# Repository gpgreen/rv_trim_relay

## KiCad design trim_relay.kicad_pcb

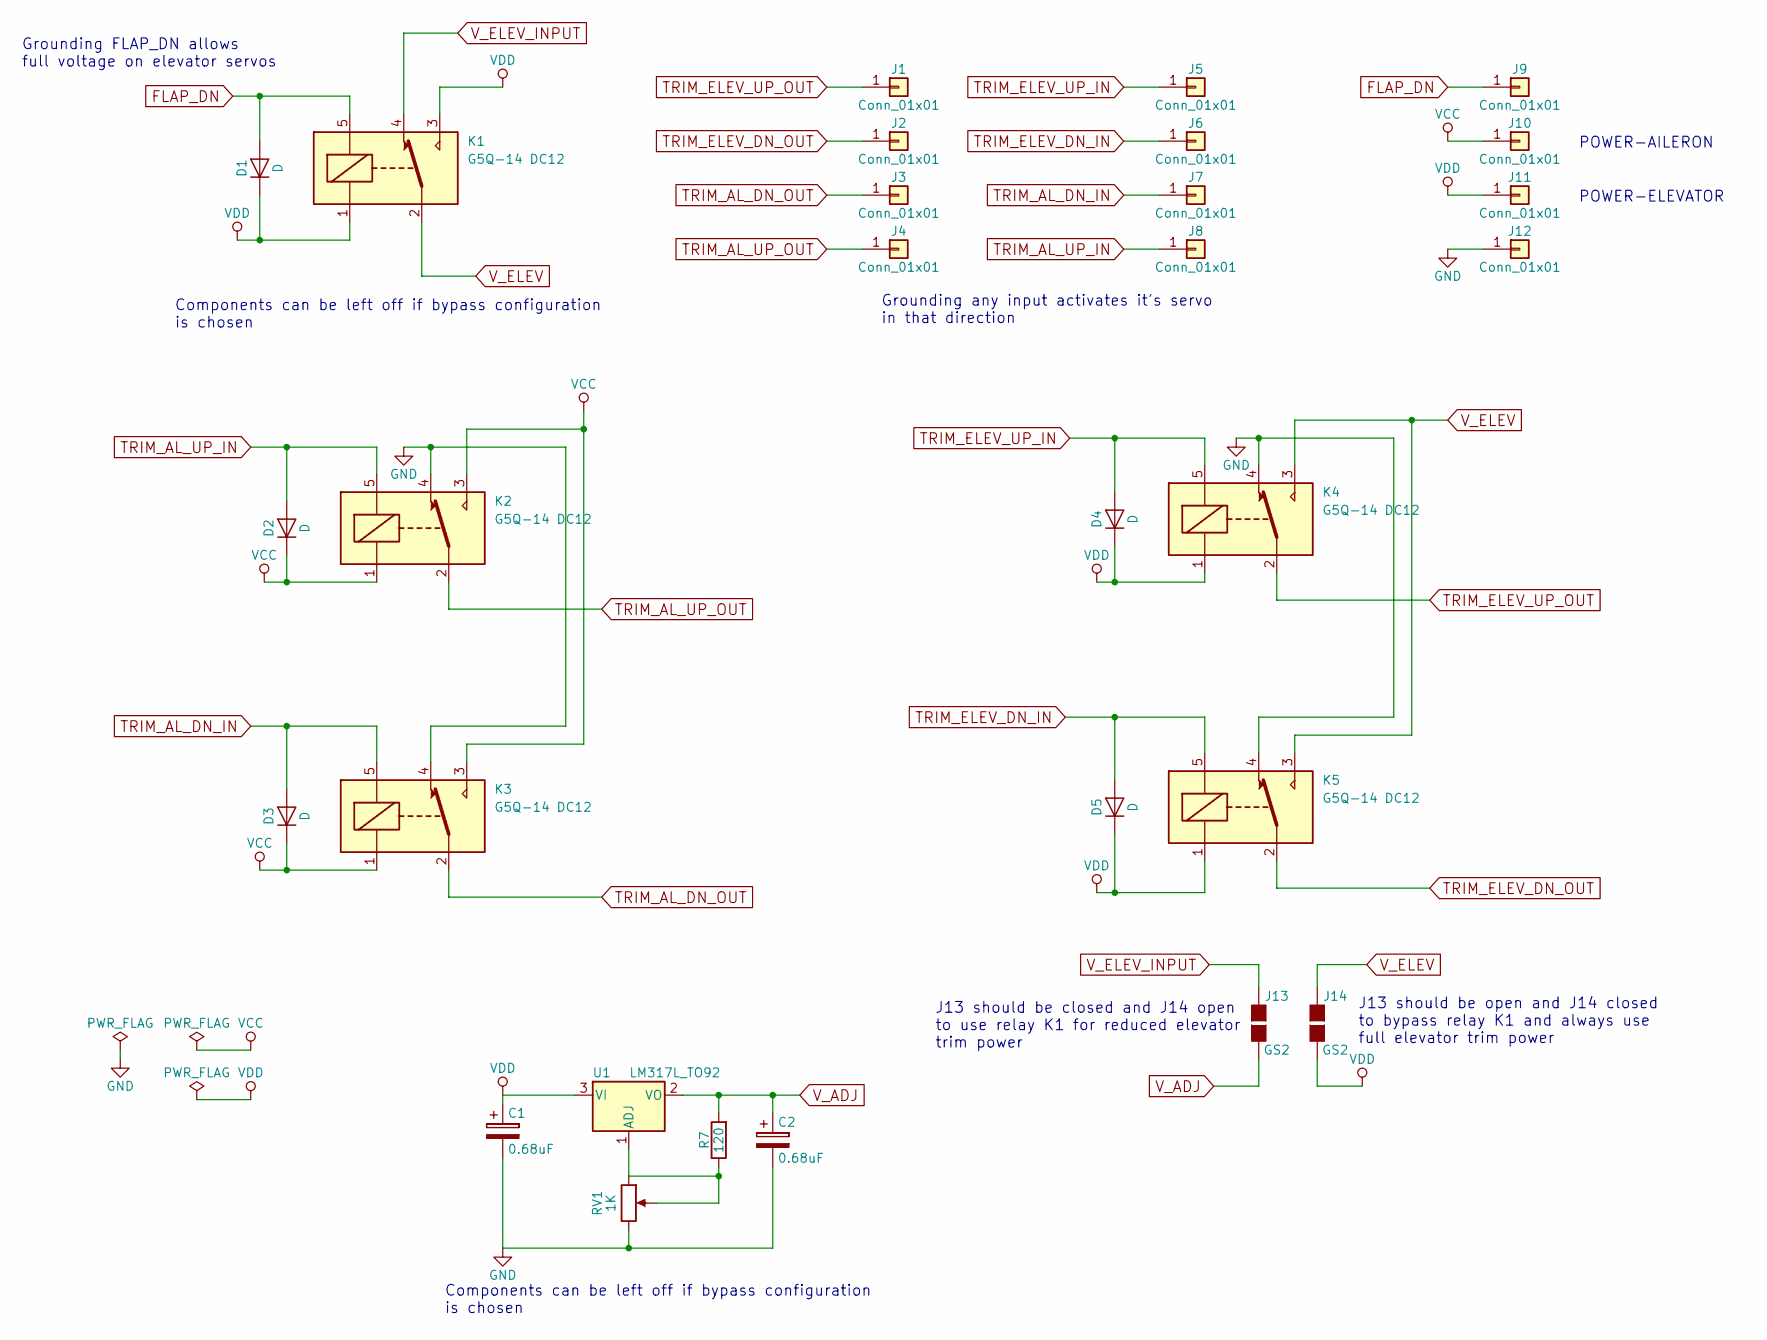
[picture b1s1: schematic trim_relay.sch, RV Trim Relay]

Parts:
C1, C2: 0.68uF; CP_Radial_D5.0mm_P2.50mm
D1, D2, D3, D4, D5: D; D_DO-41_SOD81_P10.16mm_Horizontal
J1, J2, J3, J4, J5, J6, J7, J8, J9, J10, J11, J12: Conn_01x01; FASTON-187-vert-90deg-terminal
J13, J14: GS2
K1, K2, K3, K4, K5: G5Q-14 DC12; Relay_SPDT_OMRON-G5Q
R7: 120; R_Axial_DIN0207_L6.3mm_D2.5mm_P10.16mm_Horizontal
RV1: 1K; Potentiometer_Trimmer_Copal_CT-6EP
U1: LM317L_TO92; TO-220-3_Horizontal

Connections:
FLAP_DN: D1.2 (A), J9.1, K1.5
GND: C1.2, C2.2, J12.1, K2.4, K3.4, K4.4, K5.4, RV1.3
unnamed: R7.1, RV1.1, RV1.2, U1.1 (ADJ)
TRIM_AL_DN_IN: D3.2 (A), J7.1, K3.5
TRIM_AL_DN_OUT: J3.1, K3.2
TRIM_AL_UP_IN: D2.2 (A), J8.1, K2.5
TRIM_AL_UP_OUT: J4.1, K2.2
TRIM_ELEV_DN_IN: D5.2 (A), J6.1, K5.5
TRIM_ELEV_DN_OUT: J2.1, K5.2
TRIM_ELEV_UP_IN: D4.2 (A), J5.1, K4.5
TRIM_ELEV_UP_OUT: J1.1, K4.2
VCC: D2.1 (K), D3.1 (K), J10.1, K2.1, K2.3, K3.1, K3.3
VDD: C1.1, D1.1 (K), D4.1 (K), D5.1 (K), J11.1, J14.2 (G2), K1.1, K1.3, K4.1, K5.1, U1.3 (VI)
V_ADJ: C2.1, J13.2 (G2), R7.2, U1.2 (VO)
V_ELEV: J14.1 (G1), K1.2, K4.3, K5.3
V_ELEV_INPUT: J13.1 (G1), K1.4

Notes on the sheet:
Grounding FLAP_DN allows full voltage on elevator servos
Grounding any input activates it's servo in that direction
POWER-ELEVATOR
POWER-AILERON
J13 should be closed and J14 open to use relay K1 for reduced elevator trim power
J13 should be open and J14 closed to bypass relay K1 and always use full elevator trim power
Components can be left off if bypass configuration is chosen

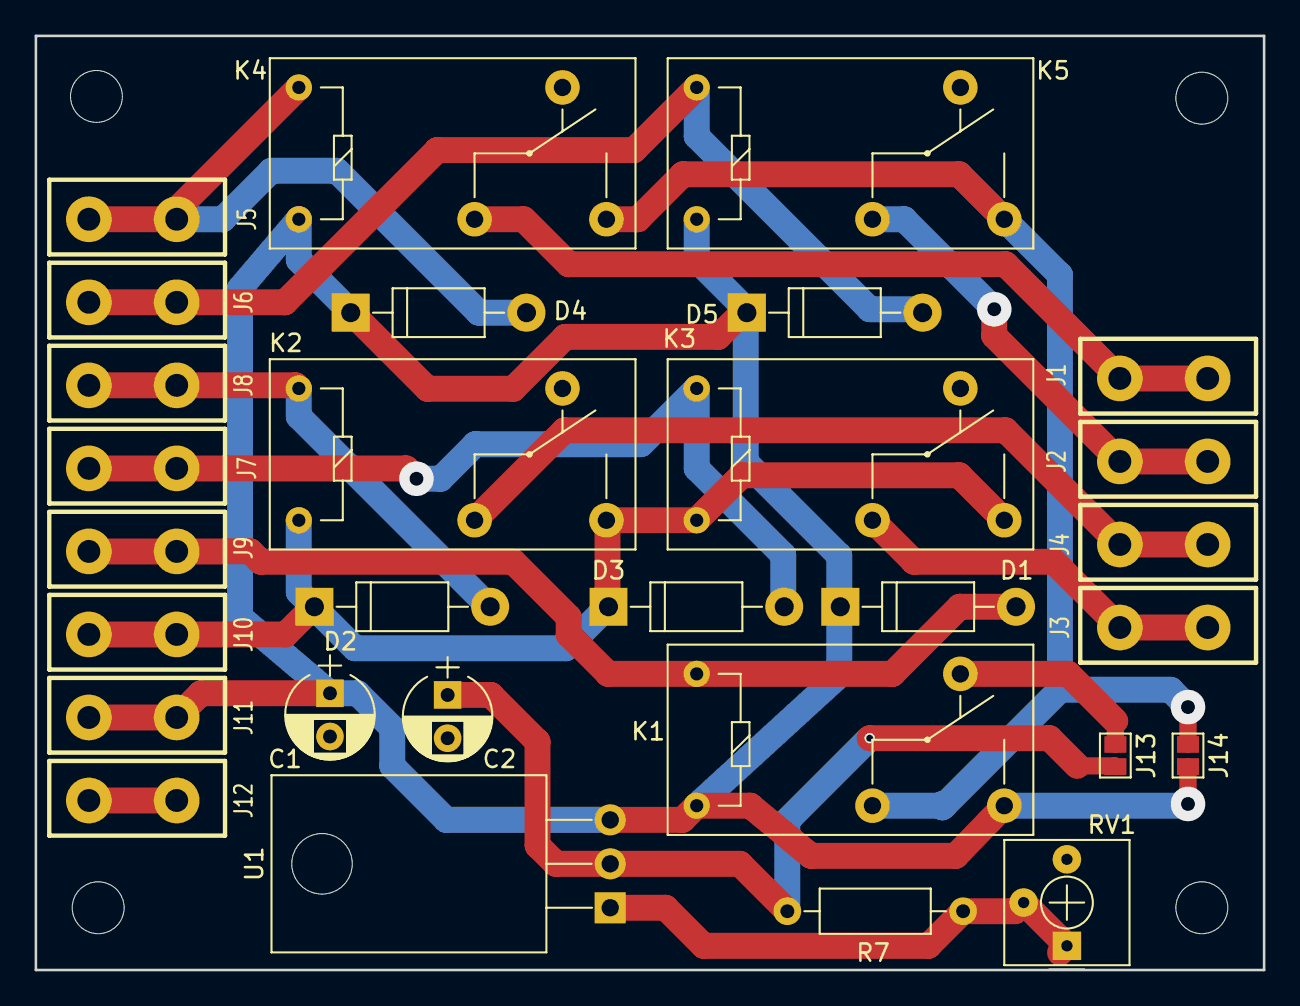
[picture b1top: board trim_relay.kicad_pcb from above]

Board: 2 copper layers, 71.0 x 54.0 mm, 29 parts (0 on the bottom side), 16 nets.

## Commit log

2018-07-31 pcb completed
2018-08-03 Changed all inputs to grounding for active
2018-08-04 Fixed layout
2018-08-05 Switch 1 power supply to 1 for each system
2018-08-05 Removed some stuff from silkscreen layer
2018-08-10 Redid schematic and pcb, removed transistors
2018-08-12 Added solder bridges, redid routing
2018-08-16 Final version
2018-09-09 Diodes were backwards
2020-12-15 new version kicad changes
2020-12-16 fixed .gitignore
